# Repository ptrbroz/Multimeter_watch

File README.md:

# An open-source multimeter watch

Contained herein is the multimeter watch project, developed by Petr Brož and David Šibrava. It is a multimeter small enough to wear on your wrist!  It utilizes the LGT8F328P-QFP32L CPU. 

The developement is ongoing, thus the project's kicad folders are split into different versions for different versions of the hardware:

# V1 prototype

The first version consists of two pcbs, mated via pin headers. The upper pcb holds the I2C display and buttons, as well as the buzzer circuit.  

The bottom pcb holds the CPU, three 3.5mm jack connectors (for custom multimeter probes) and other circuitry.

Sandwiched between the two pcbs is a Li-Po battery, rechargeable via the aforementioned pin headers.

It's features include:

- Timekeeping via I2C RTC
- Voltage, current measuring
- RLC tester functionality
- Programmable current source/sink
- Programmable I2C communication
- Buzzer

For photos of hardware, please scroll to [photos](#Photos).

# V2

The V2 hardware improves upon the V1 in several aspects:

- It changes the signal connection between the top and bottom PCBs from using pin headers to a flex cable. The boards are now held together by screws, allowing for much smaller vertical size. (~halved compared to V1 (todo:add measurements))
- 3.5 jack connectors replaced by S3B-PH-K-S connectors (jacks had poor structural integrity and would come loose with repeated insertions of probes).
- Buzzer circuitry moved to bottom PCB (to allow another slight decrease in vertical dimension).
- Various layout optimizations leading to smaller PCB footprint (42x46mm in V2 as opposed to 46x55mm in V1)

Perhaps most significant is the following improvement:

- Add alternative top PCB which utilizes capacitance-sensing buttons on the PCB itself instead of physical buttons. As the capacitance sensing is driven by an I2C device (an AT42QT1070-S located on the bottom side of the top PCB), 6 pins of the CPU are freed from being used as button inputs.

Thus, when the V2 version is used with the capacitance touch top PCB, up to 6 GPIO pins become available to the user.

# Photos

V1:
(10 CZK coin for scale (diameter = 24.5mm))

V2:
(to be photographed)

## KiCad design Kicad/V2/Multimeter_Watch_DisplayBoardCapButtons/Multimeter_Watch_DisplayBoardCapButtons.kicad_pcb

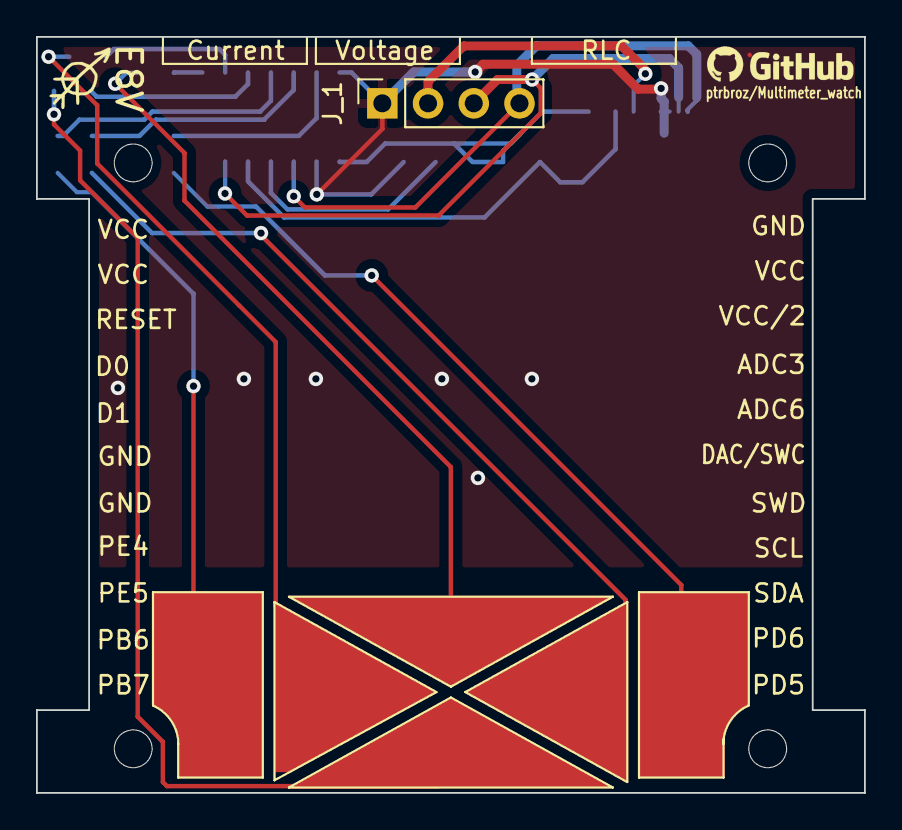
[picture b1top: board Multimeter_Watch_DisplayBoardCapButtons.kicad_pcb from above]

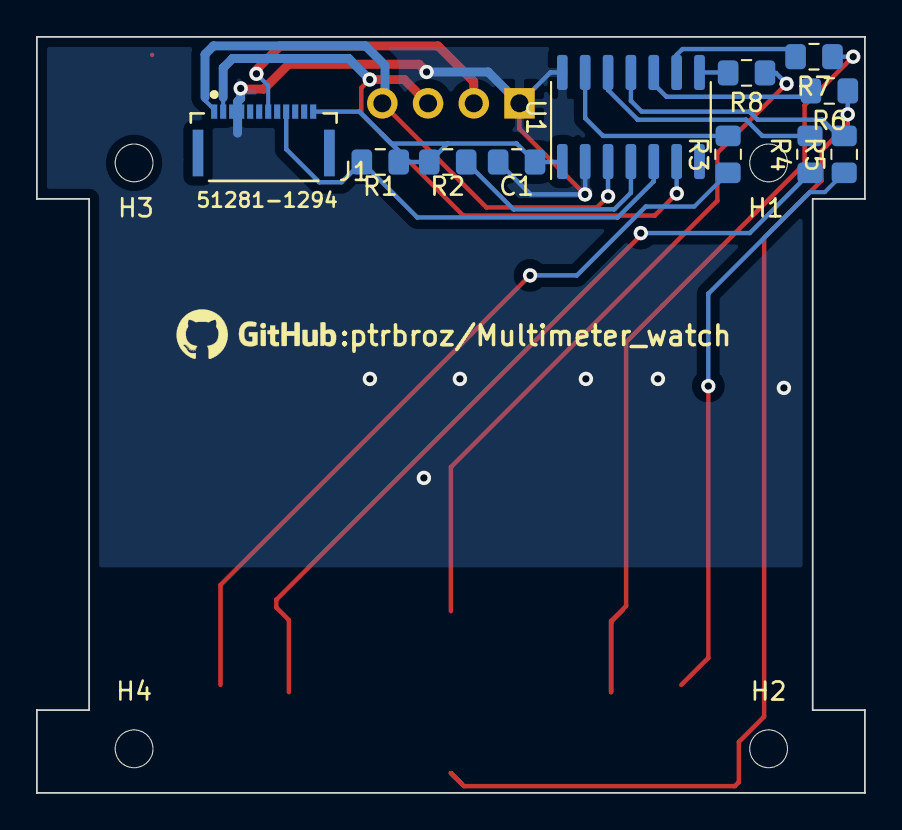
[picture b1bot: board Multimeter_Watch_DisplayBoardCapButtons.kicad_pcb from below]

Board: 2 copper layers, 46.0 x 42.0 mm, 19 parts (11 on the bottom side), 19 nets.

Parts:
 : Touch_Pad; CapButton_Right
 #2: Touch_Pad; CapButton_Left
C1: C_Small; C_0805_2012Metric_Pad1.15x1.40mm_HandSolder
DIRPAD1: CapButtons_Directional
H1, H2, H3, H4: MountingHole; MountingHole_2.1mm
J1: 51281-1294; Molex-51281-1294-Manufacturer_Recommended
J_1: Conn_01x04_Male; PinSocket_1x04_P2.54mm_Vertical
R1, R2, R3, R4, R5, R6, R7, R8: R; R_0805_2012Metric_Pad1.15x1.40mm_HandSolder
U1: AT42QT1070-S; SOIC-14_3.9x8.7mm_P1.27mm

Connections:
/GND: C1.2, J1.3, J1.4, J_1.1, U1.2, U1.14
/PB5: J1.7, J_1.2
/PB6: J1.9, R1.1, U1.5
/SCL: J1.2, J_1.3, U1.6
/SDA: J1.1, J_1.4, U1.3
/VCC: C1.1, J1.12, R1.2, R2.1, U1.1
unnamed: DIRPAD1.1, R7.1
unnamed: DIRPAD1.2, R4.1
unnamed: DIRPAD1.3, R8.1
unnamed: DIRPAD1.4, R6.1
unnamed: #2.1, R5.1
unnamed: .1, R3.1
unnamed: R2.2, U1.4
unnamed: R3.2, U1.13
unnamed: R4.2, U1.12
unnamed: R5.2, U1.11
unnamed: R6.2, U1.10
unnamed: R7.2, U1.9
unnamed: R8.2, U1.8

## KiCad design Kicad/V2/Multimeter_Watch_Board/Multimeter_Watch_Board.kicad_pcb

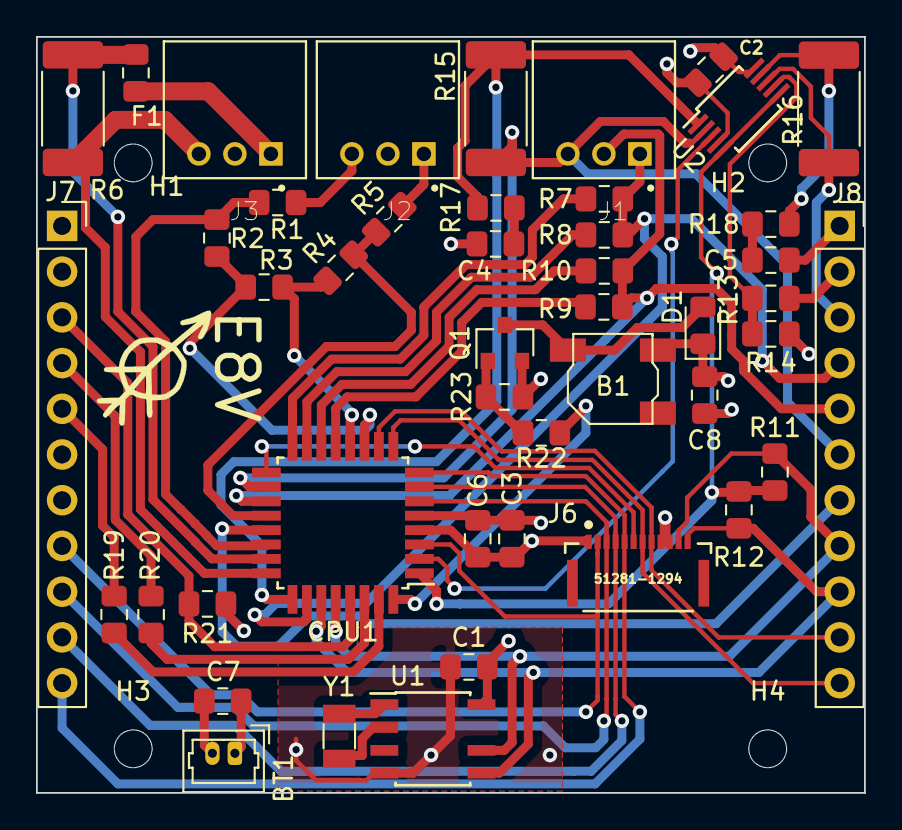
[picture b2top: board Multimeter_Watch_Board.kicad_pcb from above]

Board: 4 copper layers, 46.0 x 42.0 mm, 50 parts (0 on the bottom side), 46 nets.

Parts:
B1: CMT-0502-75-SMT-TR
BT1: Some Li-Po?; Molex_PicoBlade_53047-0210_1x02_P1.25mm_Vertical
C1, C2, C3, C8: 100n; C_0805_2012Metric_Pad1.15x1.40mm_HandSolder
C4, C5: 47p; C_0805_2012Metric_Pad1.15x1.40mm_HandSolder
C6: 10n; C_0805_2012Metric_Pad1.15x1.40mm_HandSolder
C7: 10u; C_0805_2012Metric_Pad1.15x1.40mm_HandSolder
CPU1: LGT8F328P-QFP32L; TQFP-32_7x7mm_P0.8mm
D1: D_Schottky; D_0805_2012Metric_Pad1.15x1.40mm_HandSolder
F1: Fuse; Fuse_0805_2012Metric_Pad1.15x1.40mm_HandSolder
H1, H2, H3, H4: MountingHole; MountingHole_2.1mm
J1, J2, J3: S3B-PH-K-S(LF)(SN); JST_S3B-PH-K-S(LF)(SN)
J6: 51281-1294; Molex-51281-1294-Manufacturer_Recommended
J7, J8: Conn_01x11_Female; PinSocket_1x11_P2.54mm_Vertical
Q1: A03400A N-MOS; SOT-23
R1, R5, R13, R14: 1M; R_0805_2012Metric_Pad1.15x1.40mm_HandSolder
R2, R4: 100k; R_0805_2012Metric_Pad1.15x1.40mm_HandSolder
R3: 1.43M; R_0805_2012Metric_Pad1.15x1.40mm_HandSolder
R6: 100m; R_2512_6332Metric_Pad1.52x3.35mm_HandSolder
R7, R9: 470k; R_0805_2012Metric_Pad1.15x1.40mm_HandSolder
R8, R10: 680; R_0805_2012Metric_Pad1.15x1.40mm_HandSolder
R11, R12: 4k7; R_0805_2012Metric_Pad1.15x1.40mm_HandSolder
R15, R16: 30; R_2512_6332Metric_Pad1.52x3.35mm_HandSolder
R17, R18: 200; R_0805_2012Metric_Pad1.15x1.40mm_HandSolder
R19, R20: 1k; R_0805_2012Metric_Pad1.15x1.40mm_HandSolder
R21: 10k; R_0805_2012Metric_Pad1.15x1.40mm_HandSolder
R22: 10K; R_0805_2012Metric_Pad1.15x1.40mm_HandSolder
R23: 100K; R_0805_2012Metric_Pad1.15x1.40mm_HandSolder
U1: PCF85163-SO08; SOIC-8-N7_3.9x4.9mm_P1.27mm
U2: AD8592; MSOP-10_3x3mm_P0.5mm
Y1: 32kHz; Crystal_SMD_3215-2Pin_3.2x1.5mm

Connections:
/ADC0: CPU1.23, F1.2, R6.1
/ADC1: CPU1.24, J3.3, R6.2
/ADC2: CPU1.25, R15.2, R17.2, U2.1
/ADC3: CPU1.26, J1.1, J8.4, R7.2, R8.2
/ADC6: CPU1.19, J1.2, J8.5, R9.1, R10.1
/ADC7: CPU1.22, R1.2, R2.1
/ADC10: CPU1.20, R4.2, R5.1
/D0: J7.4, R20.2
/D1: J7.5, R19.2
/DACout: CPU1.18, J1.3, J8.6, R15.1, U2.2
/GND: BT1.2, C1.1, C2.2, C3.2, C4.1, C5.1, C6.2, C7.2, C8.2, CPU1.5, J6.9, J6.10, J7.6, J7.7, J8.1, Q1.2, R14.2, R23.2, U1.4, U2.4
/PB0: CPU1.12, R3.2, R4.1
/PB1: CPU1.13, R9.2
/PB2: CPU1.14, R10.2
/PB3: CPU1.15, R8.1
/PB4: CPU1.16, R7.1
/PB5: CPU1.17, J6.6
/PB6: CPU1.7, J6.4, J7.10
/PB7: CPU1.8, J6.5, J7.11
/PD2: CPU1.32, R22.2
/PD3: CPU1.1, R11.1, R12.1, U2.5, U2.6
/PD4: CPU1.2, U2.3
/PD5: CPU1.9, J6.7, J8.11
/PD6: CPU1.10, J6.8, J8.10
/PD7: CPU1.11, R2.2, R3.1
/PE4: CPU1.3, J6.2, J7.8
/PE5: CPU1.6, J6.3, J7.9
/RESET: CPU1.29, J7.3, R21.2
/SCL: CPU1.28, J6.11, J8.8, R11.2, U1.6
/SDA: CPU1.27, J6.12, J8.9, R12.2, U1.5
/SWD: CPU1.21, J8.7
/VCC: B1.1, BT1.1, C1.2, C2.1, C3.1, C6.1, C7.1, C8.1, CPU1.4, D1.1, J6.1, J7.1, J7.2, J8.2, R13.1, R21.1, U1.8, U2.10
/VCC_HALF: J8.3, R16.1, U2.8
unnamed: B1.2, D1.2, Q1.3
unnamed: C4.2, R17.1
unnamed: C5.2, R18.1
unnamed: CPU1.30, R20.1
unnamed: CPU1.31, R19.1
unnamed: F1.1, J3.1
unnamed: J2.1, R5.2
unnamed: J2.3, R1.1
unnamed: Q1.1, R22.1, R23.1
unnamed: R13.2, R14.1, U2.7
unnamed: R16.2, R18.2, U2.9
unnamed: U1.1, Y1.2
unnamed: U1.2, Y1.1

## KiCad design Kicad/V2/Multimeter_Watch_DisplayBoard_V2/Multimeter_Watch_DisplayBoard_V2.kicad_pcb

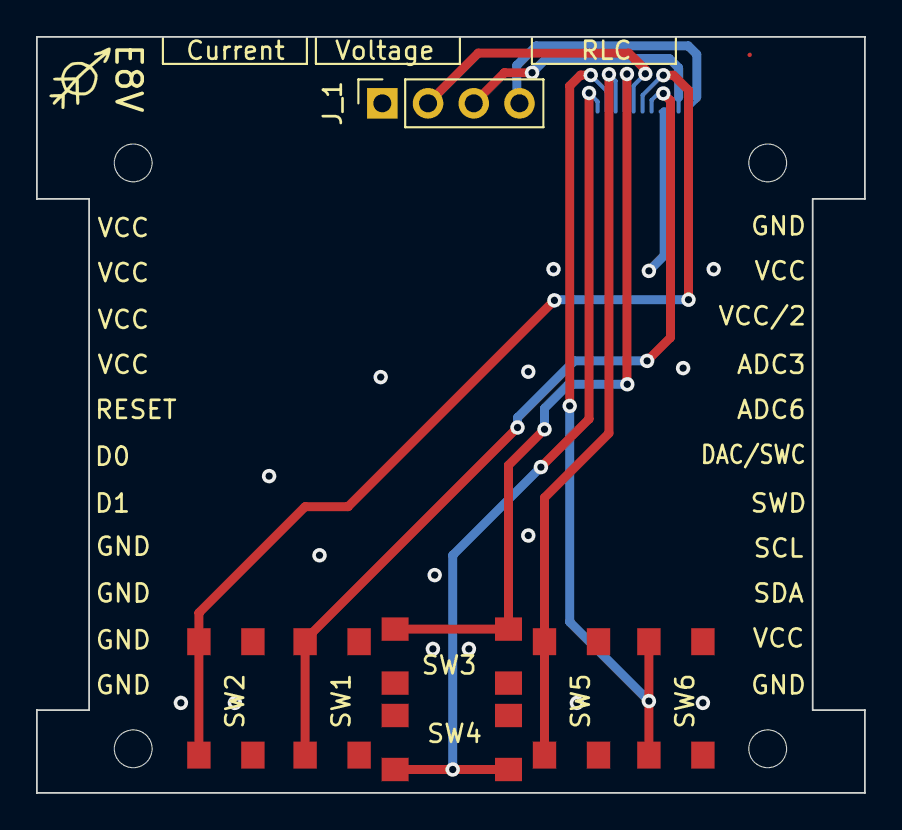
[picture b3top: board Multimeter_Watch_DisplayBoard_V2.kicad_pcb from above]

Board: 2 copper layers, 46.0 x 42.0 mm, 12 parts (1 on the bottom side), 10 nets.

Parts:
H1, H2, H3, H4: MountingHole; MountingHole_2.1mm
J1: 51281-1294; Molex-51281-1294-Manufacturer_Recommended
J_1: Conn_01x04_Male; PinSocket_1x04_P2.54mm_Vertical
SW1, SW2, SW3, SW4, SW5, SW6: SW_Push; TVCM04N

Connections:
/GND: J1.9, J1.10, J_1.1, SW1.2, SW2.2, SW3.2, SW4.2, SW5.2, SW6.2
/PB5: J1.6, J_1.2
/PB6: J1.4, SW5.1
/PB7: J1.5, SW3.1
/PD5: J1.7, SW2.1
/PD6: J1.8, SW1.1
/PE4: J1.2, SW4.1
/PE5: J1.3, SW6.1
/SCL: J1.11, J_1.3
/SDA: J1.12, J_1.4

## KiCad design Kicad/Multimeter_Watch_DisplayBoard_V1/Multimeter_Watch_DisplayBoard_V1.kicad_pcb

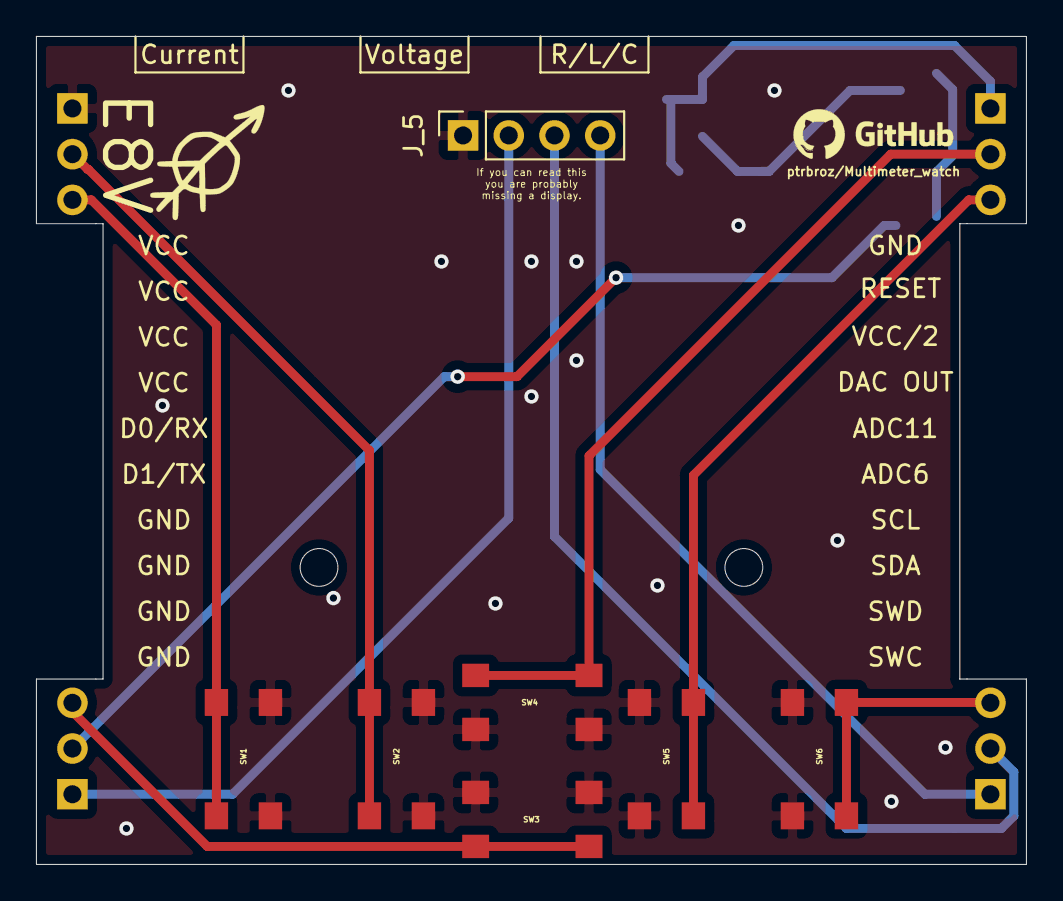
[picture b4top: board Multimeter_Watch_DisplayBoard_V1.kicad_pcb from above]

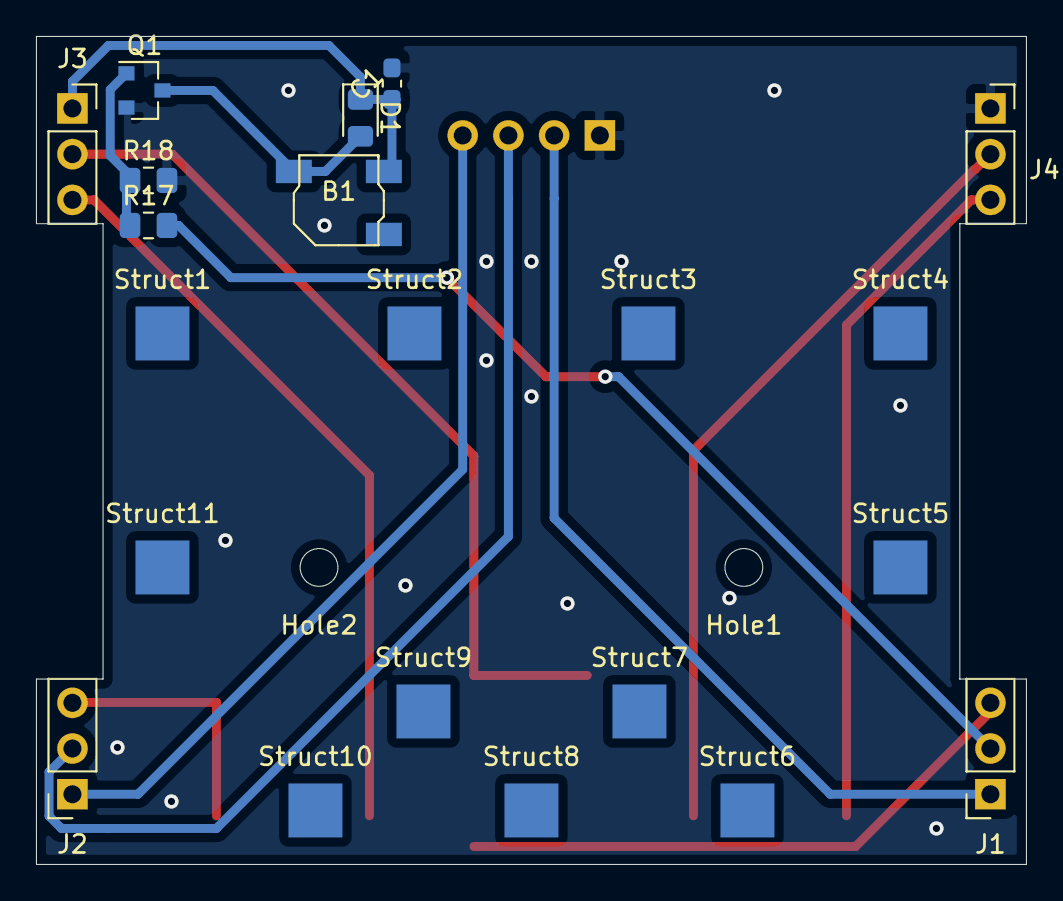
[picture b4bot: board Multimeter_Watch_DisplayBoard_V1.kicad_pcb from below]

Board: 2 copper layers, 55.0 x 46.0 mm, 30 parts (23 on the bottom side), 14 nets.

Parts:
B1: CMT-0502-75-SMT-TR
C1: 100n; C_0603_1608Metric_Pad1.05x0.95mm_HandSolder
D1: D_Schottky; D_0805_2012Metric_Pad1.15x1.40mm_HandSolder
Hole1, Hole2: MountingHole_2.1mm
J1, J2, J3, J4: Conn_01x03_Male; PinSocket_1x03_P2.54mm_Vertical
J_5: Conn_01x04_Male; PinSocket_1x04_P2.54mm_Vertical
Q1: A03400A N-MOS; SOT-23
R17: 10K; R_0805_2012Metric_Pad1.15x1.40mm_HandSolder
R18: 100K; R_0805_2012Metric_Pad1.15x1.40mm_HandSolder
SW1, SW2, SW3, SW4, SW5, SW6: SW_Push; TVCM04N
Struct1, Struct2, Struct3, Struct4, Struct5, Struct6, Struct7, Struct8, Struct9, Struct10, Struct11: StructPad

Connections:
/BUTT1: J4.2, SW2.1
/BUTT2: J4.3, SW1.1
/BUTT3: J1.3, SW3.1
/BUTT4: J3.2, SW4.1
/BUTT5: J3.3, SW5.1
/BUTT6: J2.3, SW6.1
/BUZZER: J1.2, R17.2
/ENABLE: J1.1, J_5.2
/GND: C1.2, J4.1, J_5.1, Q1.2, R18.2, SW1.2, SW2.2, SW3.2, SW4.2, SW5.2, SW6.2
/SCL: J2.2, J_5.3
/SDA: J2.1, J_5.4
/VCC: B1.1, C1.1, D1.1, J3.1
unnamed: B1.2, D1.2, Q1.3
unnamed: Q1.1, R17.1, R18.1

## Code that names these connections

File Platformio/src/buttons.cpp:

#include "Arduino.h"
#include "buttons.h"

volatile uint8_t buttonsByte = 0;
volatile uint8_t justPressedButtons = 0;
volatile uint8_t justReleasedButtons = 0;
uint8_t autoRepeatPressedButtons=0;
volatile unsigned long lastPressMillis;

  int delayBeforeAutoRepeat=400;
  int autoRepeatRate=250;


void initButtons()
{
    //button pins to inputs
    DDRD &= ~(1 << PD5);
    DDRD &= ~(1 << PD6);
    DDRB &= ~(1 << PB7);
    DDRE &= ~(1 << PE4);
    DDRB &= ~(1 << PB6);
    DDRE &= ~(1 << PE5);
    //enable pullups
    PORTD |= (1 << PD5);
    PORTD |= (1 << PD6);
    PORTB |= (1 << PB7);
    PORTE |= (1 << PE4);
    PORTB |= (1 << PB6);
    PORTE |= (1 << PE5);

    //attach interrupt to the millis timer (timer0); the rest has already been setup by millis
    OCR0A = 0xAF;
    TIMSK0 |= _BV(OCIE0A);
    //attach wakeup interrupt to left button
    PCMSK2|=(1<<PCINT21);//interrupt enable for B2
    PCICR|=(1<<PCIE0);//port B interrupt enable
}

uint8_t getButtonsByteFromPorts(uint8_t _pinB, uint8_t _pinD, uint8_t _pinE)
{
  uint8_t retVal = 0;
  retVal |= ((_pinD >> PD6) & 1) << 0; //button 1
  retVal |= ((_pinD >> PD5) & 1) << 1; //button 2
  retVal |= ((_pinE >> PE4) & 1) << 2; //button 3
  retVal |= ((_pinB >> PB7) & 1) << 3; //button 4
  retVal |= ((_pinB >> PB6) & 1) << 4; //button 5
  retVal |= ((_pinE >> PE5) & 1) << 5; //button 6
  return retVal;
}

void handleButtonEdgeDetection()
{
  justReleasedButtons = 0;
  justPressedButtons=0;
  static uint8_t lastButtonsByte;
  if (buttonsByte != lastButtonsByte)
  {
    Serial.println("BTN DET");
    justReleasedButtons = ((lastButtonsByte)) & ~buttonsByte;
    justPressedButtons = ~lastButtonsByte & buttonsByte;
    lastButtonsByte = buttonsByte;
    //Serial.println(justReleasedButtons,BIN);
  }
    if(justPressedButtons!=0)
    {
      lastPressMillis=millis();//TODO: maybe handle this in the interrupt for improved accuracy? hmmm
    }
}

void setButtonAutoRepeatRate(int _delayBeforeAutoRepeat, int _autoRepeatRate)
{
  delayBeforeAutoRepeat=_delayBeforeAutoRepeat;
  autoRepeatRate=_autoRepeatRate;
}

void resetButtonAutoRepeatRate()
{
  delayBeforeAutoRepeat=400;
  autoRepeatRate=250;
}

void handleButtonAutoRepeat()
{
  static unsigned long lastMillis=0;
  autoRepeatPressedButtons=0;
  if(millis()-lastPressMillis<delayBeforeAutoRepeat)
  {
    return;
  }
  if(millis()-lastMillis>autoRepeatRate)
  {
    autoRepeatPressedButtons=buttonsByte;
    //Serial.println(autoRepeatPressedButtons,BIN);
    lastMillis=millis();
  }
}

void handleDebouncing()
{
  static unsigned long lastMillis =0;
  static uint8_t pendingRelease;
  static uint8_t buttonsBytePhase0;
  if (millis() - lastMillis < 20)
  {
    return;
  }
  else
  {
    lastMillis = millis();
  }
  static uint8_t phase = 0;
  if (phase == 0)
  {
    pendingRelease = getButtonsByteFromPorts(PINB, PIND, PINE);
    buttonsBytePhase0 = buttonsByte;
    phase = 1;
  }
  else
  {
    uint8_t currentPendingRelease = getButtonsByteFromPorts(PINB, PIND, PINE);
    if (buttonsByte == buttonsBytePhase0 && pendingRelease == (currentPendingRelease))
    {
      //clear the pressed buttons
      buttonsByte &= ~currentPendingRelease;
    }
    phase = 0;
  }
}



SIGNAL(TIMER0_COMPA_vect)
{
  buttonsByte |= ~getButtonsByteFromPorts(PINB, PIND, PINE);
}

EMPTY_INTERRUPT(PCINT0_vect);

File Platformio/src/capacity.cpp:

#include <Arduino.h>
#include "measurement.h"
#include "capacity.h"




#include "display.h"
#include "program.h"
#include "rtcUtils.h"
#include "time.h"
#include "buttons.h"
#include "sleepUtils.h"


funRetVal cap_init( uint8_t *memPtr){
    sleep_setTimeTillSleep(-1);
    return CONTINUE_LOOP;
}

funRetVal cap_deinit( uint8_t *memPtr){
    sleep_setTimeTillSleep(10000);
    return CONTINUE_LOOP;
}

funRetVal cap_loop( uint8_t *memPtr);

const program prog_capacity = {cap_init, cap_loop,cap_deinit, "Capacity meas.", 0};

funRetVal cap_loop( uint8_t *memPtr){
    oled.set1X();
    oled.setCursor(0, 6);
    oled.print(F(">>: measure"));
    uint16_t battVolts=adc_measureBatteryVoltage();

    if (BUTT_RIGHT(justPressedButtons))
    {
        dischargeCapacitor();

        oled.set1X();
        oled.setCursor(0, 6);
        oled.print(F("Measuring..."));
        oled.set2X();
        oled.setCursor(10, 3);
        float capacity = measureCapacity3(0,battVolts);
        char temp[10];
        char temp2[20];
        getCapacityAsString(capacity, temp, 50);
        // Serial.print("Capacity: ");
        // Serial.println(temp);

        sprintf(temp2, "C: %s", temp);
        oled.print(temp2);
        oled.set1X();
        oled.setCursor(0, 6);
        oled.print(F(">>: measure"));
    }

    if (BUTT_LEFT(justPressedButtons))
    {
        oled.clear();
        return PROGRAM_END;
    }

    return CONTINUE_LOOP;
}




void testADC11()
{
    DDRB &= ~(1 << PB4);  
    DDRB &= ~(1 << PB3); //680R high side to high impedance
    DDRC &= ~(1 << PC3); //0R high side to high impedance
    //////////////////////
    PORTB &= ~(1 << PB4); //470K high side to ground
    PORTB &= ~(1 << PB3); //680R high side pullup disable
    PORTC &= ~(1 << PC3); //0R high side pullup disable
    //////////////////////
    struct adcSettings adcs;

    adc_getDefaultSettings(adcs);
    adc_adjustADCSource(adcs, adcSource_mux);
    adc_adjustMuxSource(adcs, muxSource_A3);
    adc_adjustReference(adcs, ref_1024);
    adc_applySettings(adcs);
    while(1)
    {
        Serial.println(adc_readADC());
        delay(10);
    }
}

float measureCapacity3(bool _invertPolarity,uint16_t _battVoltage)
{
    if(!_invertPolarity)
    {
        DDRB|=(1<<PB4);//470K high side to output
        DDRB&=~(1<<PB3);//680R high side to high impedance
        DDRC&=~(1<<PC3);//0R high side to high impedance
        ///////////////////////
        DDRB&=~(1<<PB1);//470K low side to high impedance
        DDRB&=~(1<<PB2);//680R low side to high impedance
        DDRE|=(1<<PE1);//0R low side to output
        //////////////////////
        PORTB&=~(1<<PB4);//470K high side to ground
        PORTB&=~(1<<PB3);//680R high side pullup disable
        PORTC&=~(1<<PC3);//0R high side pullup disable
        //////////////////////
        PORTB&=~(1<<PB1);//470k low side pullup disable
        PORTB&=~(1<<PB2);//680R low side pullup disable
        PORTE&=~(1<<PE1);//0R low side to ground

        struct adcSettings adcs;

        adc_getDefaultSettings(adcs);
        adc_adjustADCSource(adcs,adcSource_mux);
        adc_adjustMuxSource(adcs,muxSource_A3);
        adc_adjustReference(adcs,ref_1024);
        adc_applySettings(adcs);
        
        int pulsesCount=0;
        int adcReading=0;
        for(pulsesCount=0;pulsesCount<10000;pulsesCount++)
        {
            DDRB|=(1<<PB4);
            PORTB|=(1<<PB4);//470K high side to vcc
            delayMicroseconds(1000);
            DDRB&=~(1<<PB4);//470K high side to high impedance
            PORTB&=~(1<<PB4);//470K high side disable pullup
            adcReading=adc_readADC();
            if(adcReading>1000)
            {
                Serial.println(adcReading);
                Serial.println(pulsesCount);
                break;
            }
            else
            {
                if(adcReading<300&&pulsesCount>4000)
                {
                    Serial.println(adcReading);
                    Serial.println(pulsesCount);
                    Serial.println("KVAK!");
                    break;
                }
            }
        }
        float capacity=getCapacityFromAdcAndPulseCount(adcReading,pulsesCount,_battVoltage);
        return capacity;
    }
    return 0;
}

void getCapacityAsString(float _capacity, char* _outStr, int _maxLen)
{
    if(_capacity<1e-6)//<1uf
    {
        _capacity=_capacity*1e9;
        snprintf(_outStr,_maxLen,"%d nF   ",(int)_capacity);
        return;
    }
    else//>=1uf
    {
        _capacity=_capacity*1e6;
        uint32_t remainder=_capacity*10;
        remainder=remainder%10;
        snprintf(_outStr,_maxLen,"%d.%duF    ",(int)_capacity,(int)remainder);
        return;
    }
}

float getCapacityFromAdcAndPulseCount(uint16_t _adc, uint16_t _pulseCount,uint16_t _battVoltage)
{
    float t=_pulseCount*1000.0*1e-6;//time in seconds
    float Vt=(_adc/4096.0)*1.024;
    float V0=_battVoltage/1000.0;
    float R=470000;
    float capacity=-t/(R*log(1-(Vt/V0)));
    return capacity;
}

void dischargeCapacitor()
{

        DDRC|=(1<<PC3);//0R high side to output
        ///////////////////////
        DDRE|=(1<<PE1);//0R low side to output
        //////////////////////
        PORTC&=~(1<<PC3);//0R high side to ground
        //////////////////////
        PORTE&=~(1<<PE1);//0R low side to ground
        delay(100);
}

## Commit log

2020-07-15 implemented interrupt inputs (non debounced)
2020-07-16 debounced buttons, menu
2020-07-16 remove testing stuff from clockface
2020-07-17 programmer is not responding state
2020-07-18 new buttons pins, change to use internal pullups instead of external pulldowns
2020-07-18 fix debounce
2020-07-18 remove main menu scrolling flicker
2020-07-18 fix readFromSnake bug
2020-07-19 fully functional snake game (static vars yet to be joined into snakebuffer)
2020-07-19 make snake controls more responsive
2020-07-23 Rewritten control flow to new version. To be done: solve compiler not seeing program consts
    Program consts defined as they are (eg prog_snake in snake.h) don't work and cause compilation to fail. Supposedly solvable by linking all cpp files when compiling (is that possible in PIO?)
2020-07-23 Fix compilation error (wrong function signatures)
2020-07-23 move all static vars (except buffer pointer) in snake.cpp to end of snakeBuffer dynamic memory
2020-07-23 implemented stopwatch
2020-07-24 program memory is now passed as pointer from main instead of being stored in a static pointer within program
    also: fix bug in stopwatch/printSavedMeasures().
    Converted snake and stopwatch programs to new memory handling.
    Todo: convert clockface (?)
    Menu intentionally kept the same (only uses one static byte, which will never be free'd anyway)
2020-07-24 Split directories
2020-07-24 Init kicad project, add sketches
2020-07-24 make pic resolution a little less absurd (thanks, mspaint)
2020-07-24 voltage,current and rlc universal schematic part.
2020-07-24 fix shunt resistor
2020-07-24 i2c / rtc
2020-07-25 proc. board schematic (mostly) done, fist female connector version
2020-07-26 start work on pcb layout
2020-07-26 Switch left and right pin headers (for simpler DACout and VCChalf routing)
2020-07-26 first attempt at processor board layout
2020-07-27 clear board before next attempt, resize to 55x46.4mm to fit battery
2020-07-27 second layout attempt, various pinout changes for better routing
2020-07-27 Kelvin connections for shunt; minor clearance improvements.
2020-07-28 add measurements, ensure headers are symmetrical
2020-07-28 fix tracks too close after moving header
2020-07-28 measure header distance by center of hole (courtyards are not symmetrical)
2020-07-28 move I2C pullups from VCC to enable
2020-07-28 display board done, todo: move display down to allow for jack labels
2020-07-28 Add more decoupling and filtering capacitors; add series resistors for Serial port. Minor improvements.
2020-07-28 display board laid out, added silkscreen desc. of pins and jacks
2020-07-28 fix switched I2C pins
2020-07-28 add github, nouth and TGH logos
2020-07-28 actually add logos from last commit
2020-07-29 ground plane around crystal, silkscreen adjustments
2020-07-29 Add pads on bottom of displayboard
2020-07-29 rename pads
2020-07-29 reset pullup
2020-07-29 replace temp holes with actual drill holes
2020-07-29 group rlc tester pins on right header
2020-07-29 group rlc pins together on right header
2020-07-30 Moved traces from under CPU; start implementing rtc communication and sleeping.
2020-07-30 fix previous commit
2020-08-13 Refactor button handling and adjust button pinout for compatibility with the new hardware. Implement sleep + wakeup; implement r/w to RTC chip. Fix clock to correctly read the actual value from the R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
2020-08-13 Improve control loop
2020-08-13 Remove beep on startup
2020-08-13 Re-add the beep (leaving it out causes the system to crash when we run the linear power supply program for some reason)
2020-08-17 Add values for components in schematics; implement voltmeter; fix the bug where the watch goes sleep when the stopwatch is running; try implementing ohmmeter; allow the user to exit power supply app;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
2020-08-19 fix bug in hour/minute underflow caused by uint never falling below zero
2020-09-20 Create kicad folder for V2 hw
2020-09-20 pcb 46x46 area feasibility test (pre dimensions reduction)
2020-09-20 shrink pcb to 46x42
2020-09-20 wip on measuring circuits
2020-09-21 wip on V2 board
2020-09-21 V2 main board layout - first attempt
2020-09-21 fix thin dacout line
2020-09-21 clean up schematic
2020-09-22 silkscreen improvements (bottom board)
2020-09-22 displayboard layout for V2
2020-09-23 V2 displayboard silkscreen improvements, move display measurements to separate layer
2020-09-23 females layout improvements, add silkscreen labels for female pins
2020-09-24 top board rework (move flex conn up, dedicated display enable)
2020-09-28 add rlc tester protection to schematic
2020-09-28 implement rlc protection (likely to be reverted)
2020-09-29 Revert "implement rlc protection (likely to be reverted)"
    This reverts commit 3bbffdcc62f9ba327af4a0488dca8880d003efb7.
2020-09-29 Revert "add rlc tester protection to schematic"
    This reverts commit df46bc8d5560e11f4e55d6f466ca62c966db9fe4.
2020-09-29 make V2 displayboard use same pinout for buttons as V1
2020-09-29 add github to front silkscreen
2020-09-30 change kicad project naming (versions now distincted by folder)
2020-09-30 wip capacitive board - first concept of buttons shape
2020-09-30 top board capacitance buttons
2020-10-03 minor changes to capbuttons board (??)
2020-10-05 breakout button pins on bottom board
2020-10-08 move battery connector, fix silkscreen labeling of females
2020-10-08 Swiss cheese optimalizations
2020-10-11 change voltage/current connector setup from pins 1-2 to 1-3 for greater distance between voltage input pins
2020-10-12 move vcc via in rtc block
2020-10-18 Keepout and silkscreen changes to capacitance top board
2020-10-18 fix flex conn
2020-10-29 drc update and fixes to capbuttons board
2020-10-29 drc update for displayboard
2020-10-29 drc update and fixes to bottom board
2020-10-29 make touchpad reference blank
2021-01-01 add photos of V1 prototype
2021-12-28 Start developing the waveform generator and the capacitance measurement features.
2021-12-28 First working version of the arbitrary waveform generator.
2022-06-05 major refactoring; implement a formula 1 game and a non-contact voltage detector
2022-06-05 start implementing kitchen timer
2022-06-05 Unable to fix for now. Hardware differences between the Chinese clone and original seem to be present; unable to replicate the behavior of Arduino Nano with the clone; tested with clean dev board, st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
2022-06-11 Further experiments to fix the wdt.
2022-06-11 Working proof of concept with the library I found, not sure what the difference is, hmmmmm...
2022-06-11 Proof of concept of sleeping using wdt.
2022-06-11 Proof of concept implementation of the WDT
2022-06-11 Lower memory footprint to make everything work, but this needs to be solved!
2022-06-12 Fix the kitchen timer; it now works.
2022-06-12 About to merge...
2022-06-12 Completely messed up everything.
2022-06-12 Better ram reduction
2022-06-12 Implement a basic servo tester.
2022-06-18 Proof of concept of capacity measurement complete.
2022-06-19 Reimplement the sleep function in kitchen timer
2022-07-05 Hotfix memory problems.
2022-07-06 Implement basic resistance meter
2022-07-08 Improve the GUI for the reference voltage generator. Implement a sequencer command to wait for a specific time. Implement a sequencer command to wait for a button press. Implement a sequencer command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
2023-07-09 Pushing wip for diode tester.
2023-07-11 Implement snake exit without having to lose the game. Implement better redraw for the signal generator. Fix the bug with some applications preventing the watch from sleeping even once exited. Impleme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
